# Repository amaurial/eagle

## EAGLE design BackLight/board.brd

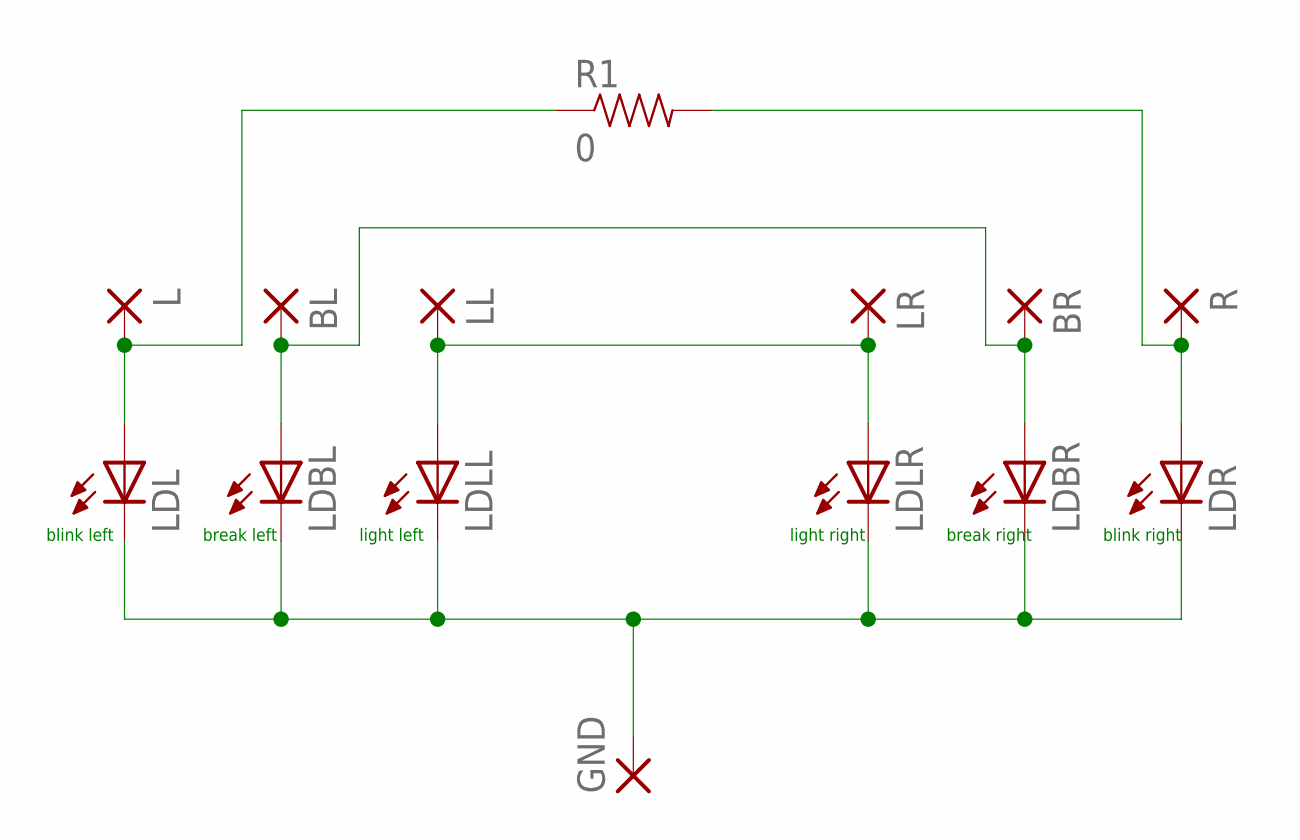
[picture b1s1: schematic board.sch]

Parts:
BL: SMD2; SMD1,27-2,54
BR: SMD2; SMD1,27-2,54
GND: SMD2; SMD1,27-2,54
L: SMD2; SMD1,27-2,54
LDBL: LEDCHIP-LED0603; CHIP-LED0603
LDBR: LEDCHIP-LED0603; CHIP-LED0603
LDL: LEDCHIP-LED0603; CHIP-LED0603
LDLL: LEDCHIP-LED0603; CHIP-LED0603
LDLR: LEDCHIP-LED0603; CHIP-LED0603
LDR: LEDCHIP-LED0603; CHIP-LED0603
LL: SMD2; SMD1,27-2,54
LR: SMD2; SMD1,27-2,54
R: SMD2; SMD1,27-2,54
R1: 0; 0603

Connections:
unnamed: GND.1, LDBL.C, LDBR.C, LDL.C, LDLL.C, LDLR.C, LDR.C
unnamed: L.1, LDL.A, R1.1
unnamed: BL.1, BR.1, LDBL.A, LDBR.A
unnamed: LDLL.A, LDLR.A, LL.1, LR.1
unnamed: LDR.A, R.1, R1.2

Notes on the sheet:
blink left
break left
light left
light right
break right
blink right

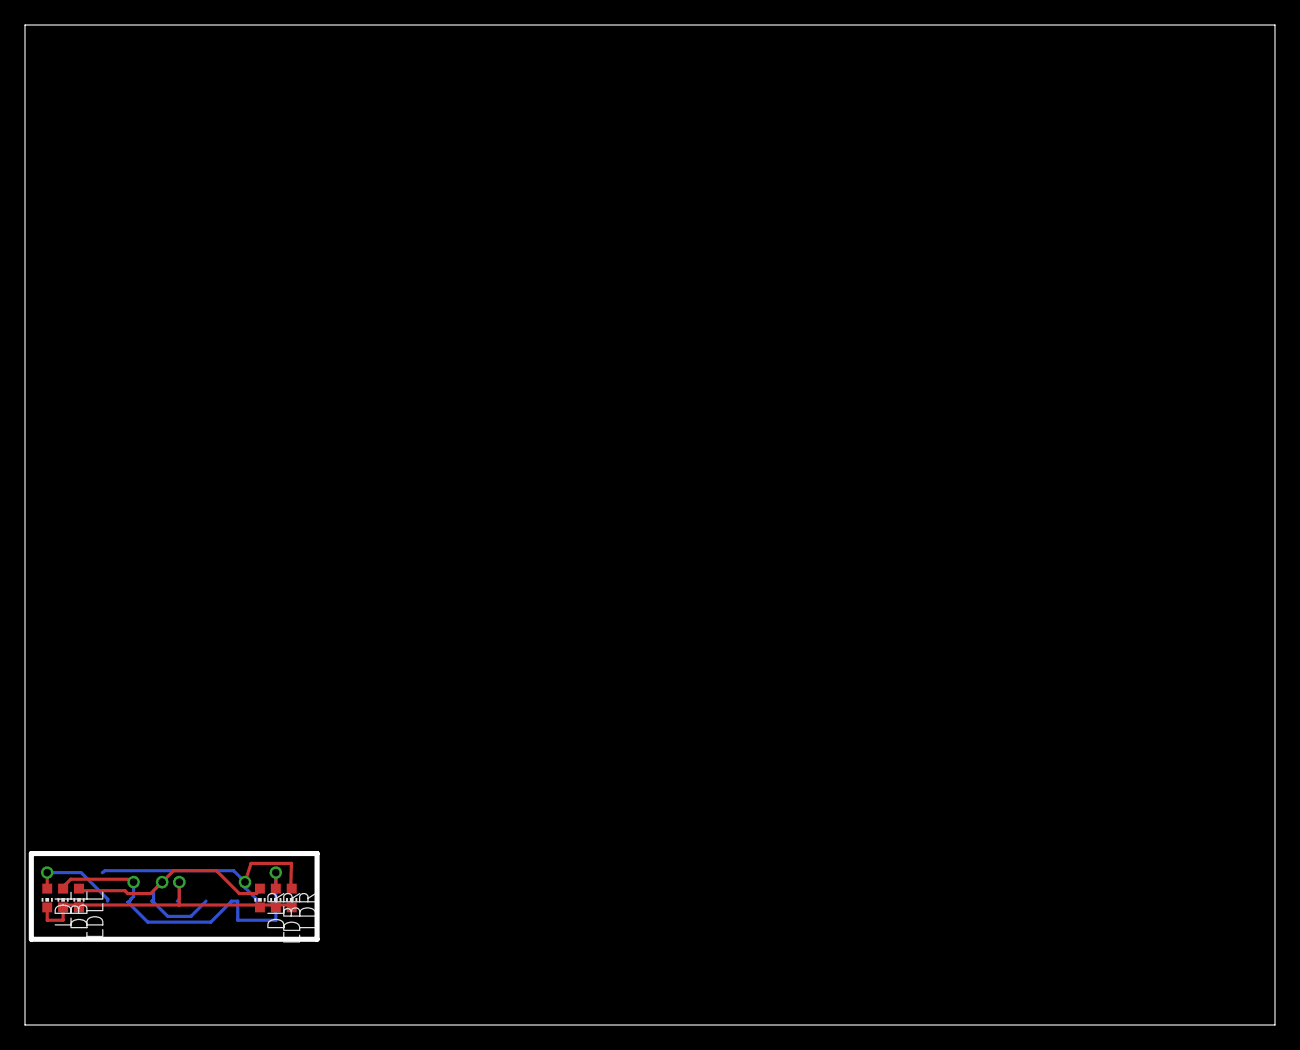
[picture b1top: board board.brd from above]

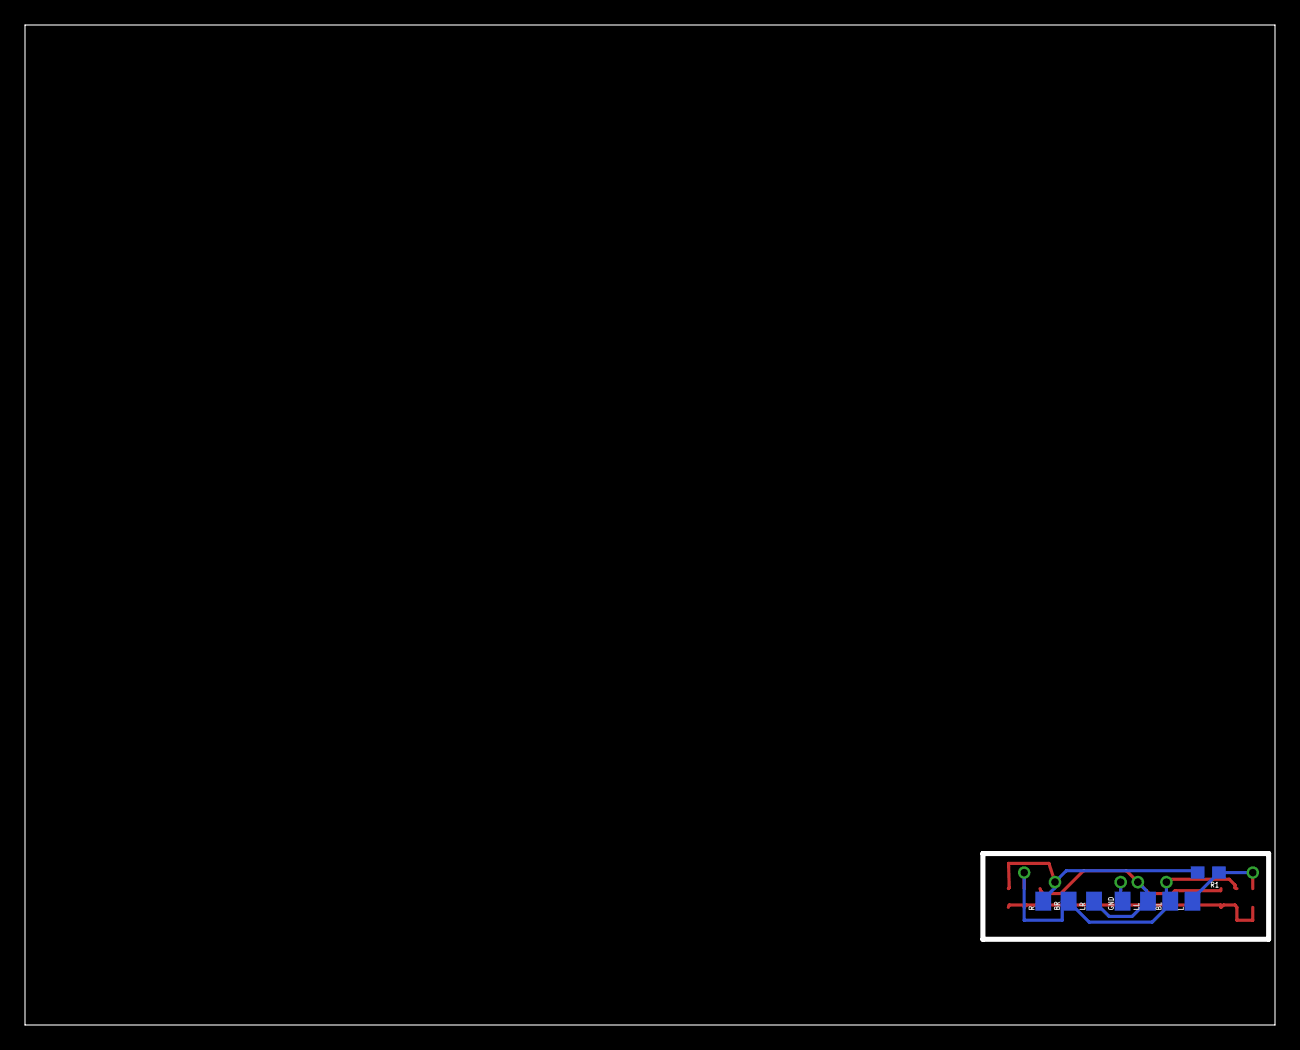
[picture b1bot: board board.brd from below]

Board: 2 copper layers, 100.0 x 80.0 mm, 14 parts (8 on the bottom side), 5 nets.

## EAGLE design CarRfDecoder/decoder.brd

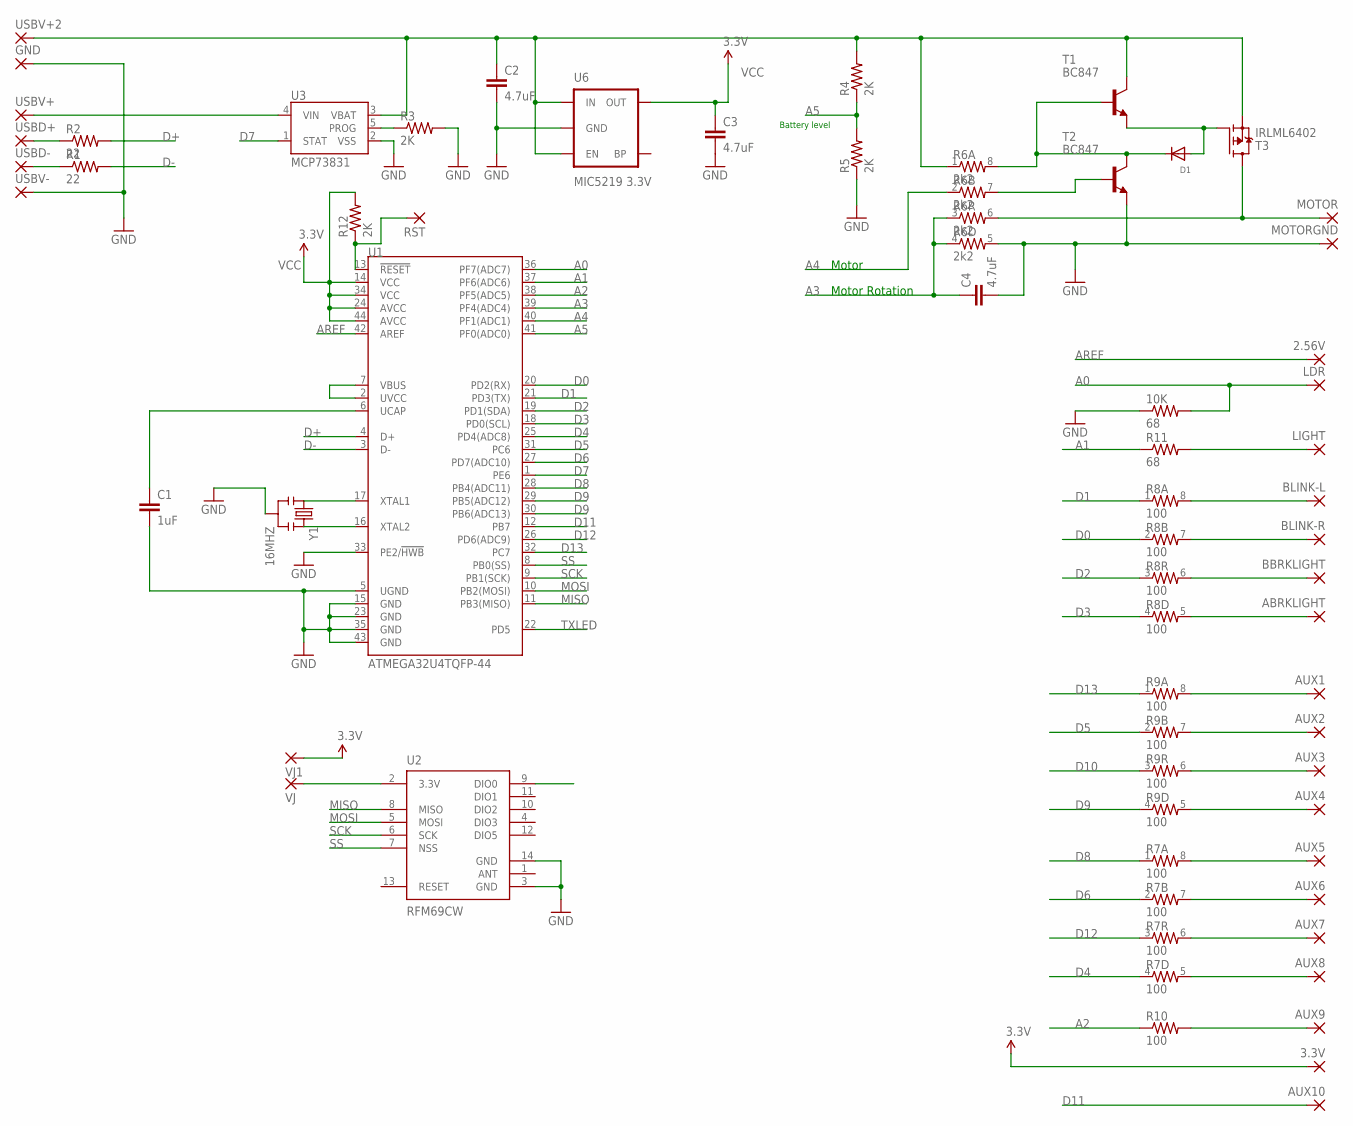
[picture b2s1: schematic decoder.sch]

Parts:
2.56V, 3.3V: SMD2; SMD1,27-2,54
10K: 68; 0603-RES
ABRKLIGHT: SMD2; SMD1,27-2,54
AUX1, AUX2, AUX3, AUX4, AUX5, AUX6, AUX7, AUX8, AUX9, AUX10: SMD2; SMD1,27-2,54
BBRKLIGHT: SMD2; SMD1,27-2,54
BLINK-L: SMD2; SMD1,27-2,54
BLINK-R: SMD2; SMD1,27-2,54
C1: 1uF; 0805
C2, C3, C4: 4.7uF; 0805
D1: DIODESOD-523; SOD-523
GND: SMD2; SMD1,27-2,54
LDR: SMD2; SMD1,27-2,54
LIGHT: SMD2; SMD1,27-2,54
MOTOR: SMD2; SMD1,27-2,54
MOTORGND: SMD2; SMD1,27-2,54
R1, R2: 22; 0603-RES
R3, R4, R5, R12: 2K; 0603-RES
R6: 2k2; 0603-ARV
R7, R8, R9: 100; 0603-ARV
R10: 100; 0603-RES
R11: 68; 0603-RES
RST: SMD2; SMD1,27-2,54
T1, T2: BC847; SOT23
T3: IRLML6402; SOT23
U1: ATMEGA32U4TQFP-44; TQFP44
U2: RFM69CW; RFM69CW-XXXS2
U3: MCP73831; SOT23-5
U6: MIC5219 3.3V; SOT23-5
USBD+: SMD2; SMD1,27-2,54
USBD-: SMD2; SMD1,27-2,54
USBV+, USBV+2: SMD2; SMD1,27-2,54
USBV-: SMD2; SMD1,27-2,54
VJ, VJ1: SMD2; SMD1,27-2,54
Y1: 16MHZ; RESONATOR-SMD

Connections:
A0: 10K.2, LDR.1, U1.36 (PF7(ADC7))
A1: R11.1, U1.37 (PF6(ADC6))
A2: R10.1, U1.38 (PF5(ADC5))
A3: C4.1, R6.3 (1), R6.4 (1), U1.39 (PF4(ADC4))
A4: R6.2 (1), U1.40 (PF1(ADC1))
A5: R4.1, R5.2, U1.41 (PF0(ADC0))
AREF: 2.56V.1, U1.42 (AREF)
D0: R8.2 (1), U1.20 (PD2(RX))
D1: R8.1, U1.21 (PD3(TX))
D2: R8.3 (1), U1.19 (PD1(SDA)), U2.9 (DIO0)
D3: R8.4 (1), U1.18 (PD0(SCL))
D4: R7.4 (1), U1.25 (PD4(ADC8))
D5: R9.2 (1), U1.31 (PC6)
D6: R7.2 (1), U1.27 (PD7(ADC10))
D7: U1.1 (PE6), U3.1 (STAT)
D8: R7.1, U1.28 (PB4(ADC11))
D9: R9.4 (1), U1.29 (PB5(ADC12))
D10: R9.3 (1), U1.30 (PB6(ADC13))
D11: AUX10.1, U1.12 (PB7)
D12: R7.3 (1), U1.26 (PD6(ADC9))
D13: R9.1, U1.32 (PC7)
D+: R2.2, U1.4 (D+)
D-: R1.2, U1.3 (D-)
GND: 10K.1, C1.2, C2.2, C3.2, C4.2, GND.1, MOTORGND.1, R3.2, R5.1, R6.5 (2), T2.2 (E), U1.5 (UGND), U1.15 (GND), U1.23 (GND), U1.33 (PE2/!HWB), U1.35 (GND), U1.43 (GND), U2.3 (GND), U2.14 (GND), U3.2 (VSS), U6.2 (GND), USBV-.1, Y1.2
MISO: U1.11 (PB3(MISO)), U2.8 (MISO)
MOSI: U1.10 (PB2(MOSI)), U2.5 (MOSI)
unnamed: C1.1, U1.6 (UCAP)
unnamed: U1.2 (UVCC), U1.7 (VBUS)
unnamed: U1.17 (XTAL1), Y1.1
unnamed: U1.16 (XTAL2), Y1.3
unnamed: R12.1, RST.1, U1.13 (!RESET)
unnamed: R2.1, USBD+.1
unnamed: R1.1, USBD-.1
unnamed: U3.4 (VIN), USBV+.1
unnamed: C2.1, R4.2, R6.1, T1.3 (C), T3.2 (S), U3.3 (VBAT), U6.1 (IN), U6.3 (EN), USBV+2.1
unnamed: R3.1, U3.5 (PROG)
unnamed: LIGHT.1, R11.2
unnamed: BLINK-L.1, R8.8 (2)
unnamed: D1.A, T1.2 (E), T3.1 (G)
unnamed: MOTOR.1, R6.6 (2), T3.3 (D)
unnamed: BLINK-R.1, R8.7 (2)
unnamed: R6.7 (2), T2.1 (B)
unnamed: BBRKLIGHT.1, R8.6 (2)
unnamed: D1.K (C), R6.8 (2), T1.1 (B), T2.3 (C)
unnamed: ABRKLIGHT.1, R8.5 (2)
unnamed: AUX1.1, R9.8 (2)
unnamed: AUX2.1, R9.7 (2)
unnamed: AUX3.1, R9.6 (2)
unnamed: AUX4.1, R9.5 (2)
unnamed: AUX5.1, R7.8 (2)
unnamed: AUX6.1, R7.7 (2)
unnamed: AUX7.1, R7.6 (2)
unnamed: AUX8.1, R7.5 (2)
unnamed: AUX9.1, R10.2
unnamed: U2.2 (3.3V), VJ.1
SCK: U1.9 (PB1(SCK)), U2.6 (SCK)
SS: U1.8 (PB0(SS)), U2.7 (NSS)
TXLED: U1.22 (PD5)
VCC: 3.3V.1, C3.1, R12.2, U1.14 (VCC), U1.24 (AVCC), U1.34 (VCC), U1.44 (AVCC), U6.5 (OUT), VJ1.1

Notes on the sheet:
Battery level
Motor
Motor Rotation

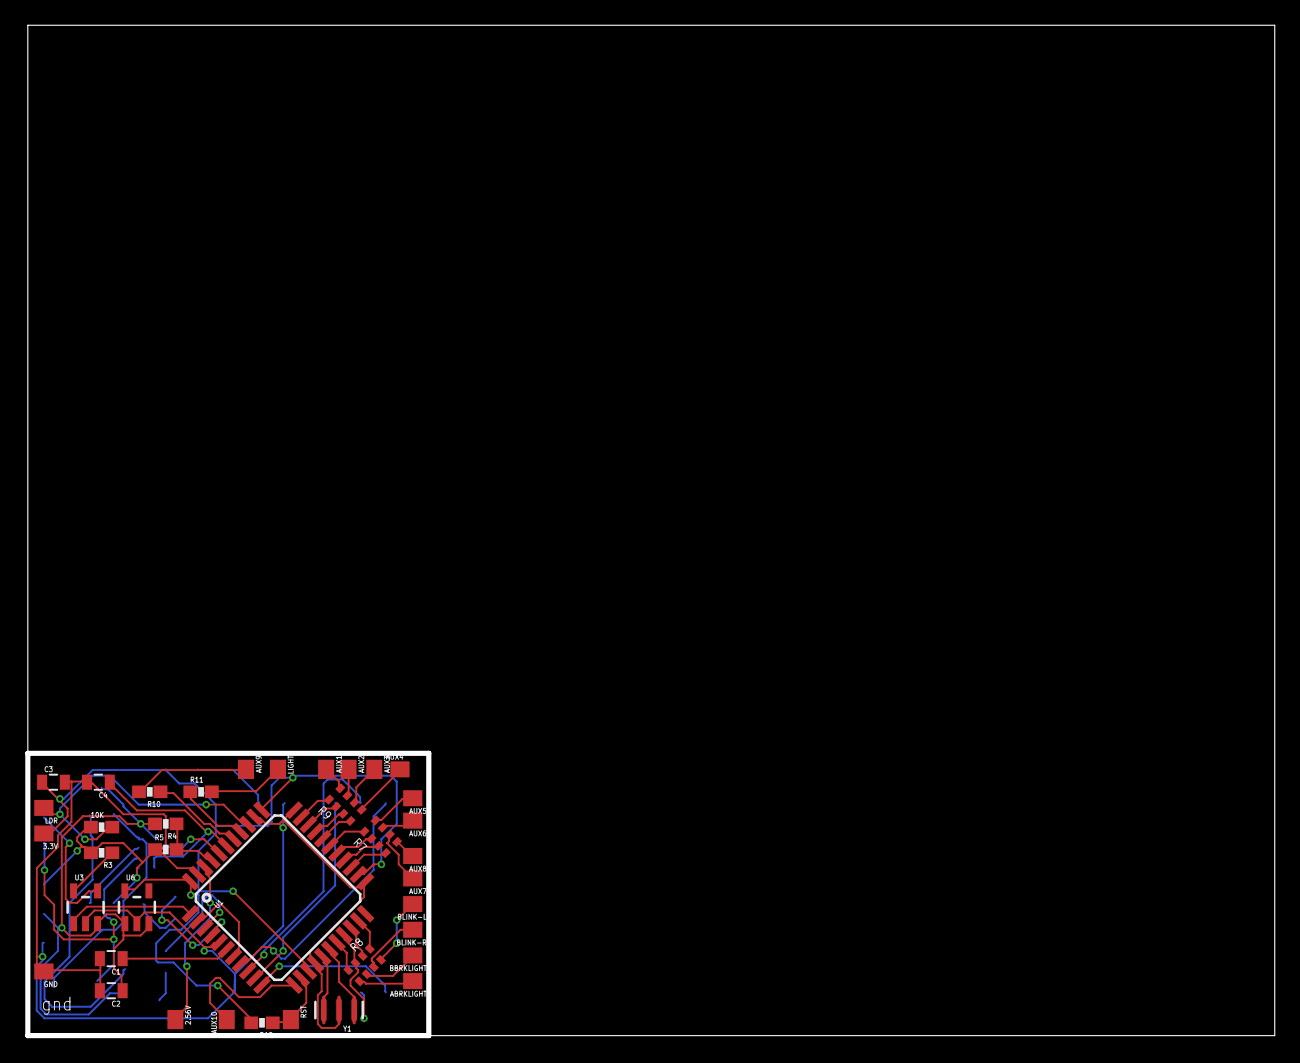
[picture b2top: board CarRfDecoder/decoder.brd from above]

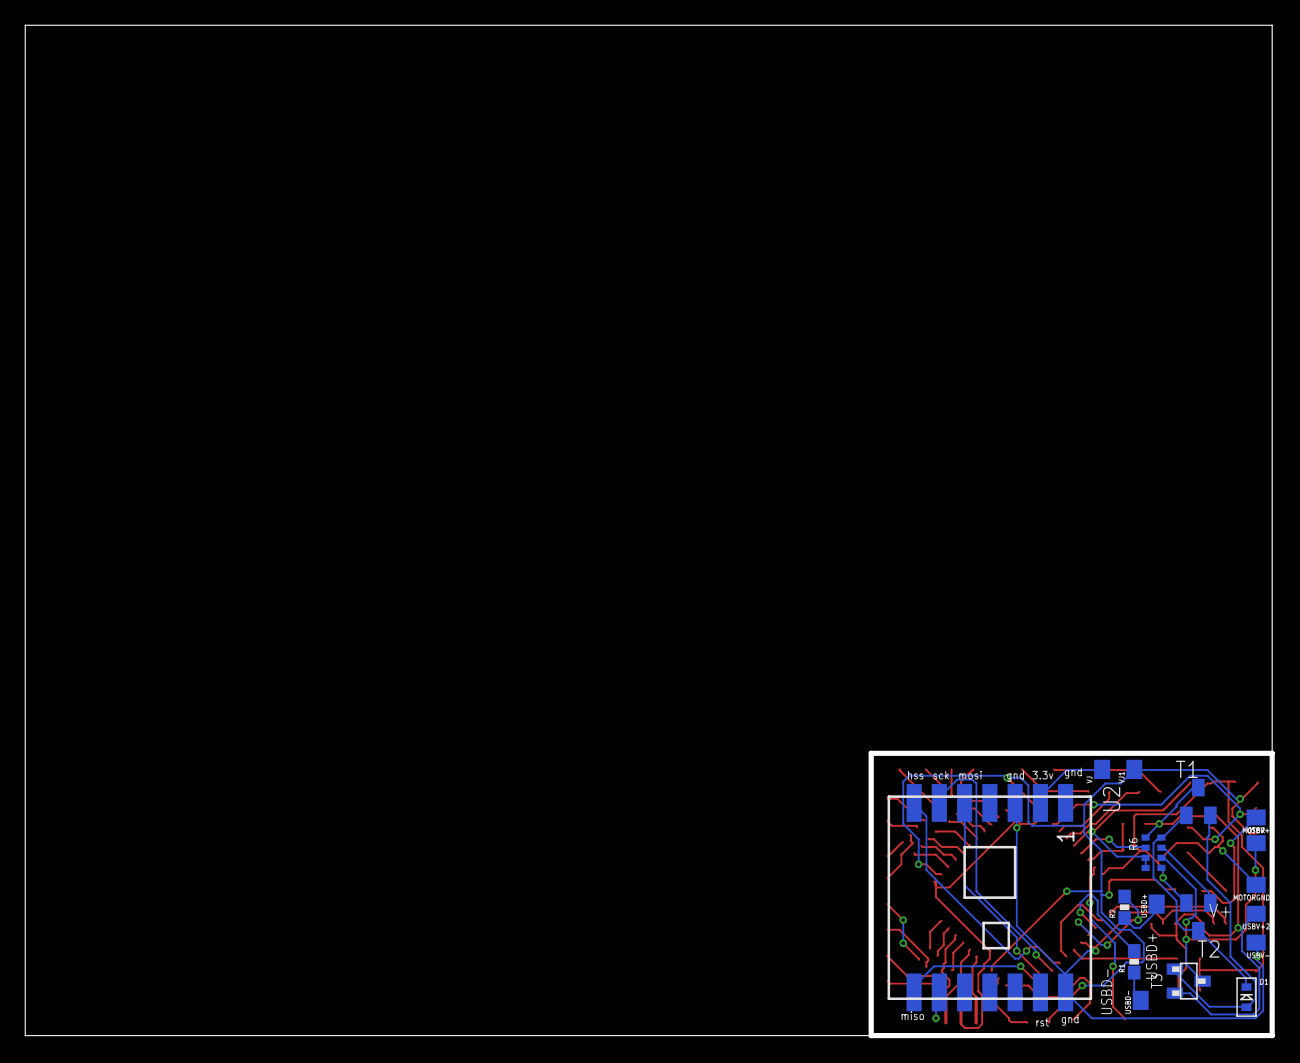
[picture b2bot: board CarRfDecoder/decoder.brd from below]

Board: 2 copper layers, 98.7 x 80.0 mm, 55 parts (17 on the bottom side), 58 nets.

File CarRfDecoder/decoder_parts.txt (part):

<<<<<<< HEAD
Partlist exported from /home/amaurial/eagle/CarRfDecoder/decoder.sch at 19/08/15 8:48 PM

Part      Value             Device                 Package       Description                                                                             PROD_ID    VALUE       
2.56V                       SMD2                   SMD1,27-2,54  SMD PAD                                                                                                        
3.3V                        SMD2                   SMD1,27-2,54  SMD PAD                                                                                                        
10K       68                RESISTOR0603-RES       0603-RES      Resistor                                                                                                       
ABRKLIGHT                   SMD2                   SMD1,27-2,54  SMD PAD                                                                                                        
AUX1                        SMD2                   SMD1,27-2,54  SMD PAD                                                                                                        
AUX2                        SMD2                   SMD1,27-2,54  SMD PAD                                                                                                        
AUX3                        SMD2                   SMD1,27-2,54  SMD PAD                                                                                                        
AUX4                        SMD2                   SMD1,27-2,54  SMD PAD                                                                                                        
AUX5                        SMD2                   SMD1,27-2,54  SMD PAD                                                                                                        
AUX6                        SMD2                   SMD1,27-2,54  SMD PAD                                                                                                        
AUX7                        SMD2                   SMD1,27-2,54  SMD PAD                                                                                                        
AUX8                        SMD2                   SMD1,27-2,54  SMD PAD                                                                                                        
AUX9                        SMD2                   SMD1,27-2,54  SMD PAD                                                                                                        
AUX10                       SMD2                   SMD1,27-2,54  SMD PAD                                                                                                        
BBRKLIGHT                   SMD2                   SMD1,27-2,54  SMD PAD                                                                                                        
BLINK-L                     SMD2                   SMD1,27-2,54  SMD PAD                                                                                                        
BLINK-R                     SMD2                   SMD1,27-2,54  SMD PAD                                                                                                        
C1        1uF               CAP0805                0805          Capacitor                                                                                                      
C2        4.7uF             CAP0805                0805          Capacitor                                                                                                      
C3        4.7uF             CAP0805                0805          Capacitor                                                                                                      
C4        4.7uF             CAP0805                0805          Capacitor                                                                                                      
D1                          DIODESOD-523           SOD-523       Diode                                                                                                          
GND                         SMD2                   SMD1,27-2,54  SMD PAD                                                                                                        
LDR                         SMD2                   SMD1,27-2,54  SMD PAD                                                                                                        
LIGHT                       SMD2                   SMD1,27-2,54  SMD PAD                                                                                                        
MOTOR                       SMD2                   SMD1,27-2,54  SMD PAD                                                                                                        
MOTORGND                    SMD2                   SMD1,27-2,54  SMD PAD                                                                                                        
R1        22                RESISTOR0603-RES       0603-RES      Resistor                                                                                                       
R2        22                RESISTOR0603-RES       0603-RES      Resistor                                                                                                       
R3        2K                RESISTOR0603-RES       0603-RES      Resistor                                                                                                       
R4        2K                RESISTOR0603-RES       0603-RES      Resistor                                                                                                       
R5        2K                RESISTOR0603-RES       0603-RES      Resistor                                                                                                       
R6        2k2               RESISTOR-ARRAY0603-ARV 0603-ARV      Array Chip Resistor                                                                                            
R7        100               RESISTOR-ARRAY0603-ARV 0603-ARV      Array Chip Resistor                                                                                            
R8        100               RESISTOR-ARRAY0603-ARV 0603-ARV      Array Chip Resistor                                                                                            
R9        100               RESISTOR-ARRAY0603-ARV 0603-ARV      Array Chip Resistor                                                                                            
R10       100               RESISTOR0603-RES       0603-RES      Resistor                                                                                                       
R11       68                RESISTOR0603-RES       0603-RES      Resistor                                                                                                       
T1        BC847             BC847                  SOT23         NPN TRANSISTOR                                                                                                 
T2        BC847             BC847                  SOT23         NPN TRANSISTOR                                                                                                 
T3        IRLML6402         MOSFET-P-SOT23         SOT23         P-Channel MOSFET (e.g.  IRLML6402)                                                                             
U1        ATMEGA32U4TQFP-44 ATMEGA32U4TQFP-44      TQFP44        Atmel 44-pin 8-bit Microcontroller with 32KBytes of ISP Flash and USB Controller                               
U2        RFM69CW           RFM69CW                RFM69CW-XXXS2                                                                                                                
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
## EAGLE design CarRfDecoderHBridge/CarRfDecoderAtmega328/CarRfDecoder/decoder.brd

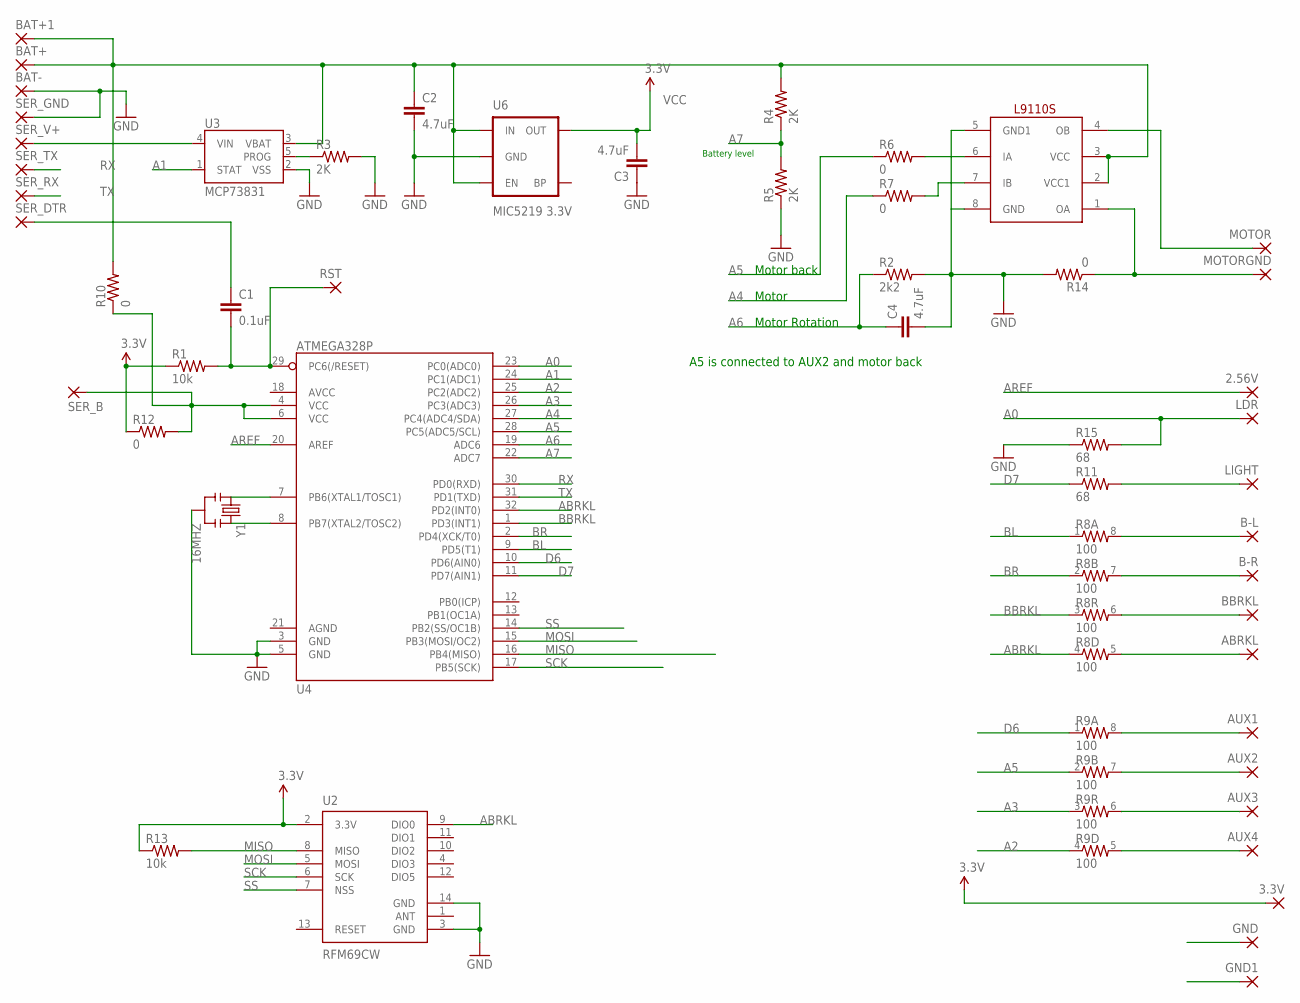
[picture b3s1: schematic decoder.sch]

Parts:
2.56V, 3.3V: SMD2; SMD1,27-2,54
ABRKL: SMD2; SMD1,27-2,54
AUX1, AUX2, AUX3, AUX4: SMD2; SMD1,27-2,54
B-L: SMD2; SMD1,27-2,54
B-R: SMD2; SMD1,27-2,54
BAT+, BAT+1: SMD2; SMD1,27-2,54
BAT-: SMD2; SMD1,27-2,54
BBRKL: SMD2; SMD1,27-2,54
C1: 0.1uF; 0805
C2, C3, C4: 4.7uF; 0805
GND, GND1: SMD2; SMD1,27-2,54
LDR: SMD2; SMD1,27-2,54
LIGHT: SMD2; SMD1,27-2,54
MDRIVER: L9110S; SO08
MOTOR: SMD2; SMD1,27-2,54
MOTORGND: SMD2; SMD1,27-2,54
R1, R13: 10k; 0603-RES
R2: 2k2; 0603-RES
R3, R4, R5: 2K; 0603-RES
R6, R7, R10, R12, R14: 0; 0603-RES
R8, R9: 100; 0603-ARV
R11, R15: 68; 0603-RES
RST: SMD2; SMD1,27-2,54
SER_B: SMD2; SMD1,27-2,54
SER_DTR: SMD2; SMD1,27-2,54
SER_GND: SMD2; SMD1,27-2,54
SER_RX: SMD2; SMD1,27-2,54
SER_TX: SMD2; SMD1,27-2,54
SER_V+: SMD2; SMD1,27-2,54
U2: RFM69CW; RFM69CW-XXXS2
U3: MCP73831; SOT23-5
U4: ATMEGA328P; TQFP32-08
U6: MIC5219 3.3V; SOT23-5
Y1: 16MHZ; RESONATOR-SMD

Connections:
A0: LDR.1, R15.2, U4.23 (PC0(ADC0))
A1: U3.1 (STAT), U4.24 (PC1(ADC1))
A2: R9.4 (1), U4.25 (PC2(ADC2))
A3: R9.3 (1), U4.26 (PC3(ADC3))
A4: R7.1, U4.27 (PC4(ADC4/SDA))
A5: R6.1, R9.2 (1), U4.28 (PC5(ADC5/SCL))
A6: C4.1, R2.1, U4.19 (ADC6)
A7: R4.1, R5.2, U4.22 (ADC7)
ABRKL: R8.4 (1), U2.9 (DIO0), U4.32 (PD2(INT0))
AREF: 2.56V.1, U4.20 (AREF)
BAT+: BAT+.1, BAT+1.1, C2.1, MDRIVER.2 (VCC1), MDRIVER.3 (VCC), R4.2, R10.2, U3.3 (VBAT), U6.1 (IN), U6.3 (EN)
BBRKL: R8.3 (1), U4.1 (PD3(INT1))
BL: R8.1, U4.9 (PD5(T1))
BR: R8.2 (1), U4.2 (PD4(XCK/T0))
D6: R9.1, U4.10 (PD6(AIN0))
D7: R11.1, U4.11 (PD7(AIN1))
GND: BAT-.1, C2.2, C3.1, C4.2, GND.1, GND1.1, MDRIVER.5 (GND1), MDRIVER.8 (GND), R2.2, R3.2, R5.1, R14.2, R15.1, SER_GND.1, U2.3 (GND), U2.14 (GND), U3.2 (VSS), U4.3 (GND), U4.5 (GND), U6.2 (GND), Y1.2
MISO: R13.2, U2.8 (MISO), U4.16 (PB4(MISO))
MOSI: U2.5 (MOSI), U4.15 (PB3(MOSI/OC2))
unnamed: U4.7 (PB6(XTAL1/TOSC1)), Y1.1
unnamed: C1.1, SER_DTR.1
unnamed: U4.8 (PB7(XTAL2/TOSC2)), Y1.3
unnamed: C1.2, R1.2, RST.1, U4.29 (PC6(/RESET))
unnamed: MDRIVER.6 (IA), R6.2
unnamed: MDRIVER.7 (IB), R7.2
unnamed: R10.1, R12.2, SER_B.1, U4.4 (VCC), U4.6 (VCC)
unnamed: SER_V+.1, U3.4 (VIN)
unnamed: R3.1, U3.5 (PROG)
unnamed: LIGHT.1, R11.2
unnamed: B-L.1, R8.8 (2)
unnamed: B-R.1, R8.7 (2)
unnamed: BBRKL.1, R8.6 (2)
unnamed: ABRKL.1, R8.5 (2)
unnamed: AUX1.1, R9.8 (2)
unnamed: AUX2.1, R9.7 (2)
unnamed: AUX3.1, R9.6 (2)
unnamed: AUX4.1, R9.5 (2)
OA: MDRIVER.1 (OA), MOTORGND.1, R14.1
OB: MDRIVER.4 (OB), MOTOR.1
RX: SER_TX.1, U4.30 (PD0(RXD))
SCK: U2.6 (SCK), U4.17 (PB5(SCK))
SS: U2.7 (NSS), U4.14 (PB2(SS/OC1B))
TX: SER_RX.1, U4.31 (PD1(TXD))
VCC: 3.3V.1, C3.2, R1.1, R12.1, R13.1, U2.2 (3.3V), U6.5 (OUT)

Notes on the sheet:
Battery level
Motor
Motor Rotation
Motor back
A5 is connected to AUX2 and motor back

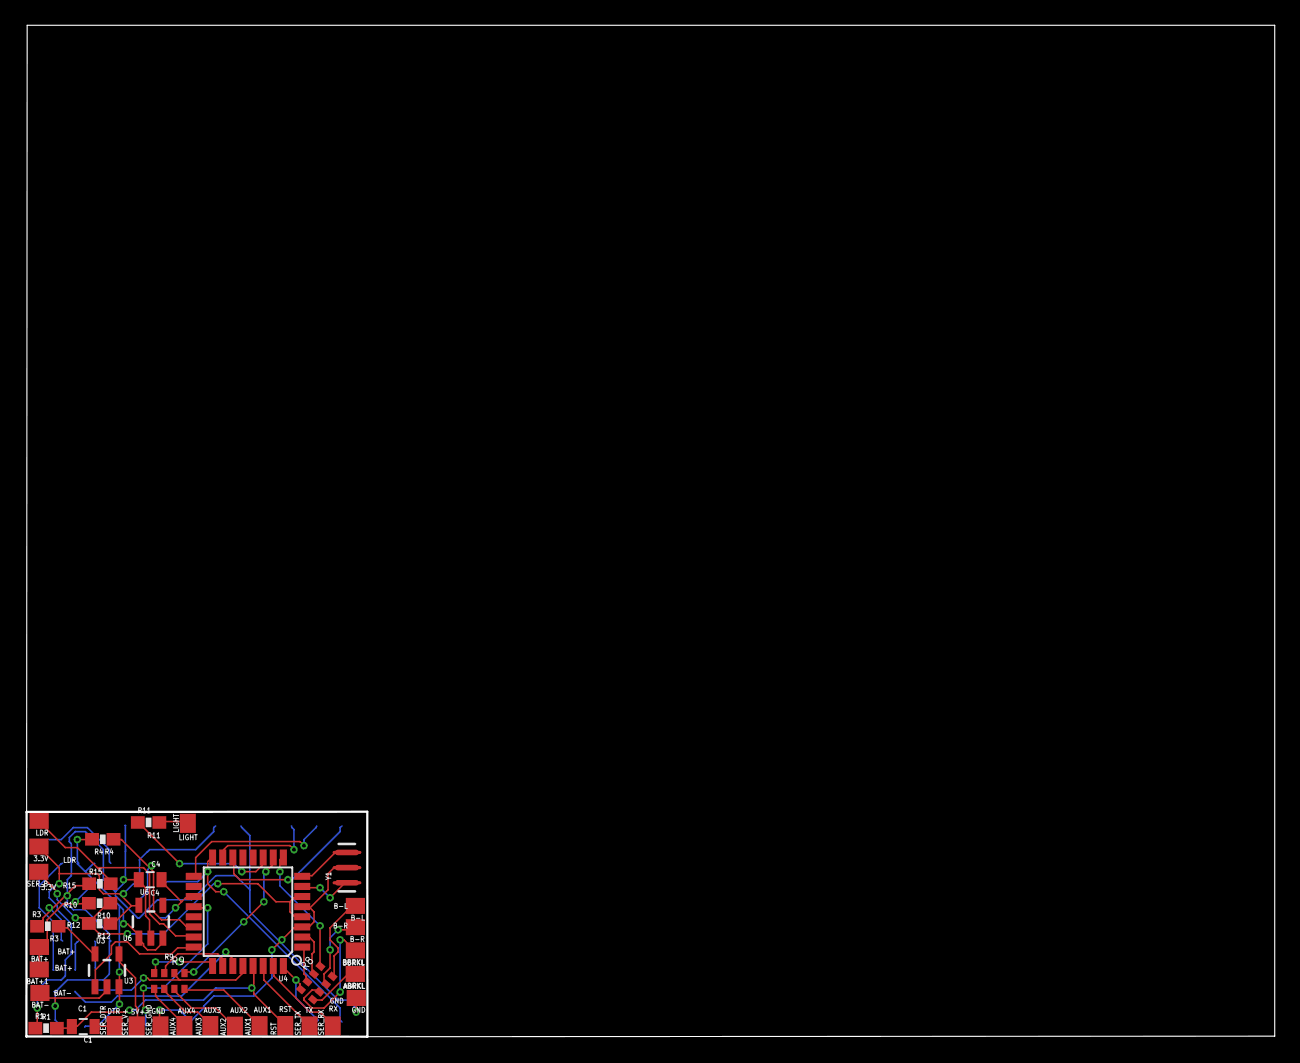
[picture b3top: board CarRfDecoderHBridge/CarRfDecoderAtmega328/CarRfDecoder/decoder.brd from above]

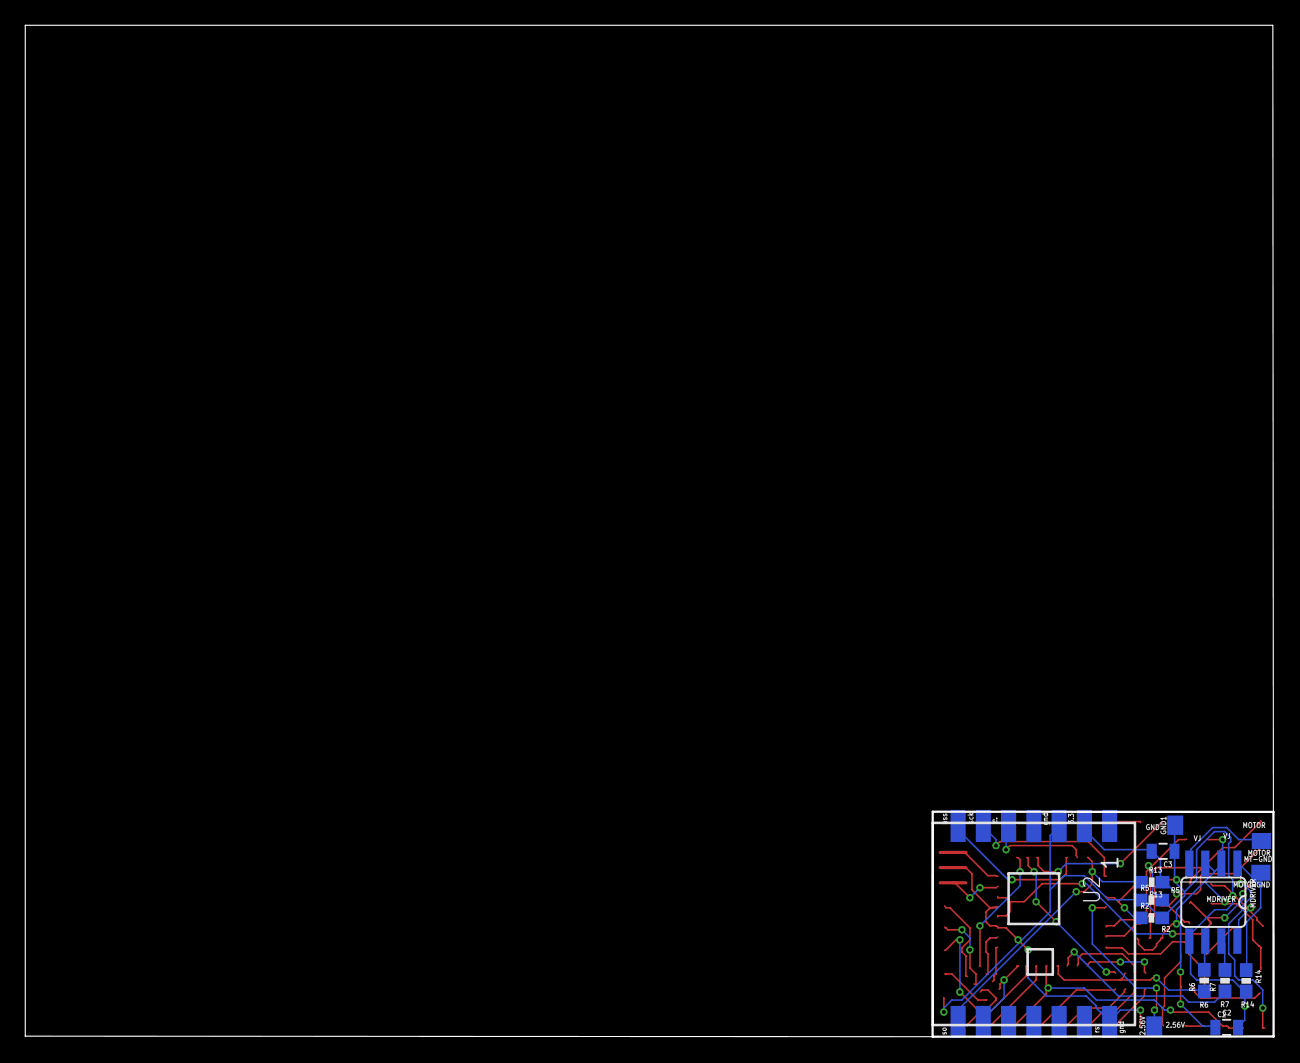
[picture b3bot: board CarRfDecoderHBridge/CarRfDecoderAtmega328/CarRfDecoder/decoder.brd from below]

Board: 2 copper layers, 98.8 x 80.0 mm, 51 parts (14 on the bottom side), 44 nets.

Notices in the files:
parts and their libraries:
SparkFun-Resistors: Licensing: Creative Commons ShareAlike 4.0 International - https://creativecommons.org/licenses/by-sa/4.0
diy-modules: Released under the Creative Commons Attribution 4.0 International License: http://creativecommons.org/licenses/by/4.0
